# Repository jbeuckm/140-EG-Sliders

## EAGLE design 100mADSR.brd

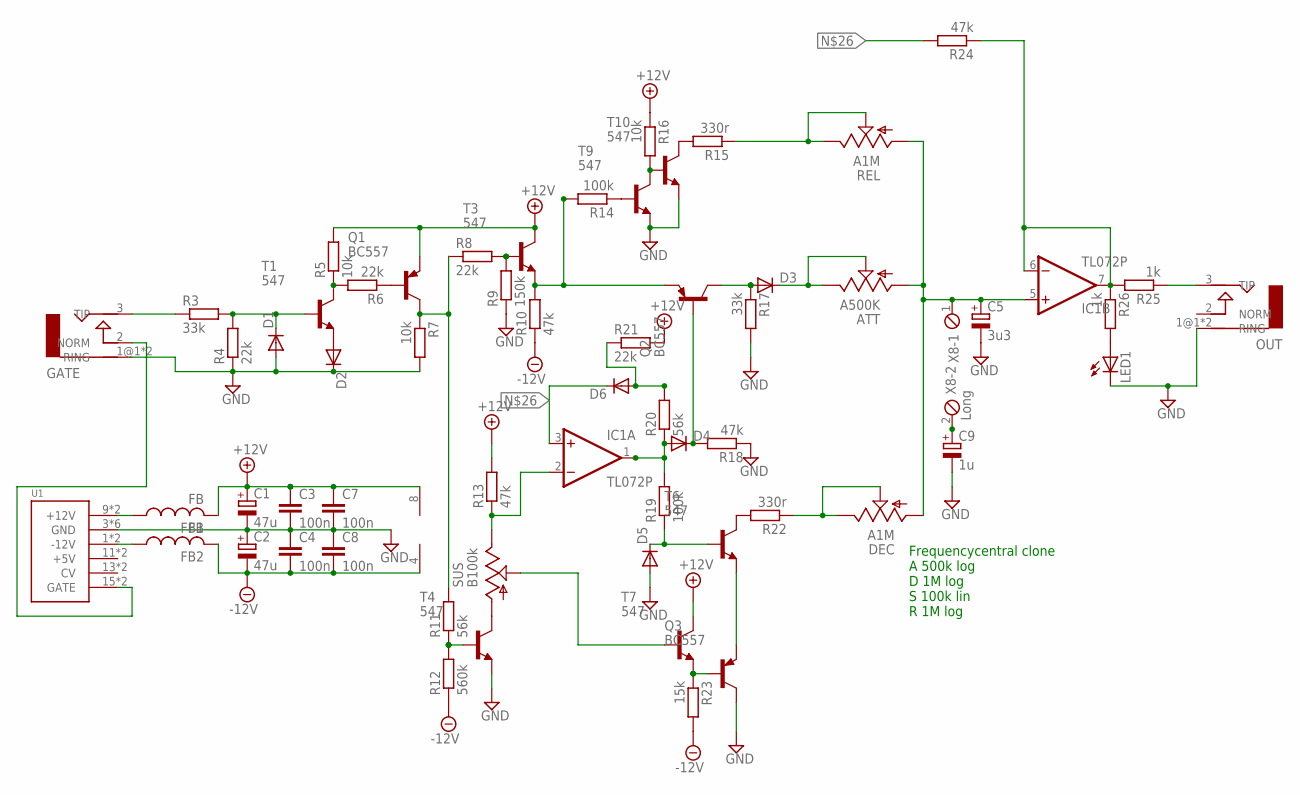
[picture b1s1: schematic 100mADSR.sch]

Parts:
ATT: A500K; SLIDEPOT-45
C1, C2: 47u; E2,5-7
C3, C4: 100n; C025-025X050
C5: 3u3; E2,5-6
C7, C8: 100n; C1206K
C9: 1u; E2,5-6
D1, D2, D3, D4, D5, D6: 1N4148DO35-7; DO35-7
DEC: A1M; SLIDEPOT-45
FB1, FB2: FB
GATE: AUDIO-JACKERTHENVAR; ERTHENVAR-JACK
IC1: TL072P; DIL08
LED1: LED3MM
OUT: AUDIO-JACKERTHENVAR; ERTHENVAR-JACK
Q1, Q2, Q3: BC557; TO92-EBC
R3, R17: 33k; 0204/7
R4, R6, R8, R21: 22k; 0204/7
R5, R7, R16: 10k; 0204/7
R9: 150k; 0204/7
R10, R13, R18, R24: 47k; 0204/7
R11, R20: 56k; 0204/7
R12: 560k; 0204/7
R14, R19: 100k; 0204/7
R15, R22: 330r; 0204/7
R23: 15k; 0204/7
R25, R26: 1k; 0204/7
REL: A1M; SLIDEPOT-45
SUS: B100k; SLIDEPOT-45
T1, T3, T4, T6, T7, T9, T10: 547; TO92-CBE
U1: POWER; POWER_16
X8: Long; 2POL254

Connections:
+12V: C1.+, C3.1, C7.1, FB1.P$2 (2), IC1.8 (V+), Q1.E, R5.2, R13.2, R16.1, R21.2, T3.C, T7.C
-12V: C2.-, C4.2, C8.2, FB2.P$2 (2), IC1.4 (V-), R10.1, R12.1, R23.2
GND: C1.-, C2.+, C3.2, C4.1, C5.-, C7.2, C8.1, C9.-, D1.A, D2.C, D5.A, GATE.1@1 (RING), GATE.1@2 (RING), LED1.K (C), OUT.1@1 (RING), OUT.1@2 (RING), Q3.C, R4.1, R7.2, R9.1, R17.2, R18.1, T4.E, T9.E, T10.E, U1.3 (GND), U1.4 (GND), U1.5 (GND), U1.6 (GND), U1.7 (GND), U1.8 (GND)
unnamed: OUT.3 (TIP), R25.1
unnamed: R14.1, T9.B
unnamed: R16.2, T9.C, T10.B
unnamed: R15.2, T10.C
unnamed: R15.1, REL.B, REL.WIPER
unnamed: SUS.A, T4.C
unnamed: D3.A, Q2.C, R17.1
unnamed: D4.C, Q2.B, R18.2
unnamed: D1.C, R3.2, R4.2, T1.B
unnamed: Q1.B, R6.1
unnamed: R5.1, R6.2, T1.C
unnamed: R11.1, R12.2, T4.B
unnamed: GATE.2 (NORM), U1.15 (GATE), U1.16 (GATE)
unnamed: IC1.2 (-IN), R13.1, SUS.B
unnamed: D6.A, R20.2, R21.1
unnamed: D2.A, T1.E
unnamed: Q1.C, R7.1, R8.1, R11.2
unnamed: D4.A, IC1.1 (OUT), R19.2, R20.1
unnamed: R8.2, R9.2, T3.B
unnamed: Q2.E, R10.2, R14.2, T3.E
unnamed: D5.C, R19.1, T6.B
unnamed: R22.2, T6.C
unnamed: Q3.E, T6.E
unnamed: Q3.B, R23.1, T7.E
unnamed: SUS.WIPER, T7.B
unnamed: D6.C, IC1.3 (+IN), R24.2
unnamed: LED1.A, R26.2
unnamed: ATT.B, ATT.WIPER, D3.C
unnamed: DEC.B, DEC.WIPER, R22.1
unnamed: ATT.A, C5.+, DEC.A, IC1.5 (+IN), REL.A, X8.1
unnamed: IC1.6 (-IN), IC1.7 (OUT), R24.1, R25.2, R26.1
unnamed: GATE.3 (TIP), R3.1
unnamed: C9.+, X8.2
unnamed: FB1.P$1 (1), U1.9 (+12V), U1.10 (+12V)
unnamed: FB2.P$1 (1), U1.1 (-12V), U1.2 (-12V)

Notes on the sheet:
Frequencycentral clone A 500k log D 1M log S 100k lin R 1M log

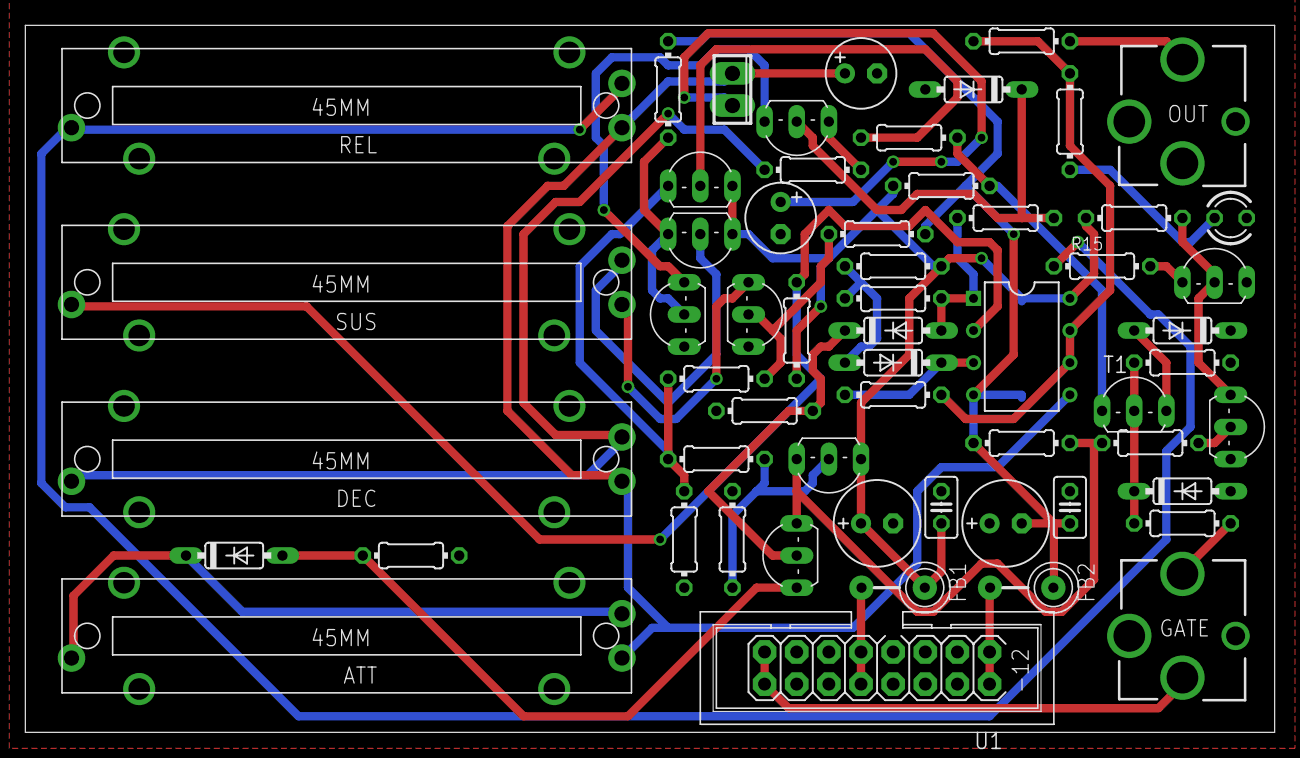
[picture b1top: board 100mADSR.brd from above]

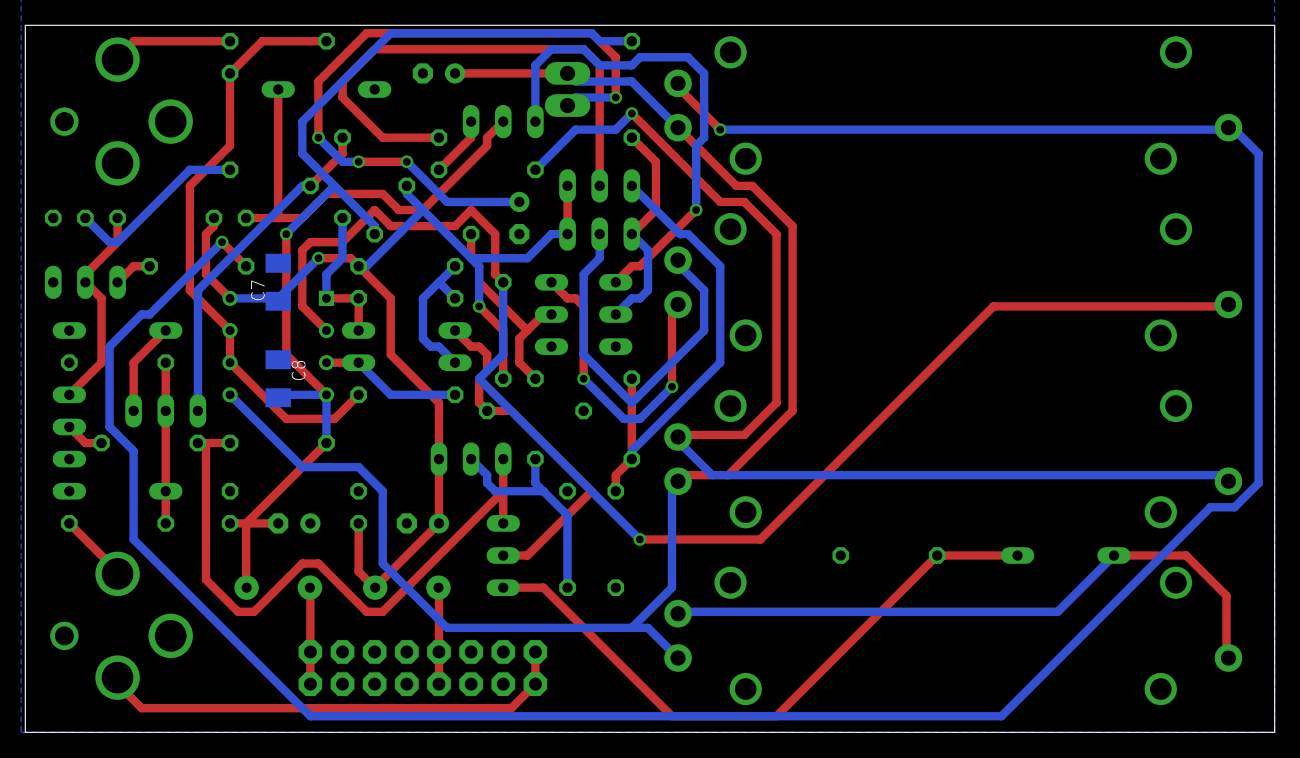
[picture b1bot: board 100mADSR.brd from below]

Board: 2 copper layers, 98.7 x 55.9 mm, 60 parts (2 on the bottom side), 38 nets.

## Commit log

2017-08-27 fixed labels
